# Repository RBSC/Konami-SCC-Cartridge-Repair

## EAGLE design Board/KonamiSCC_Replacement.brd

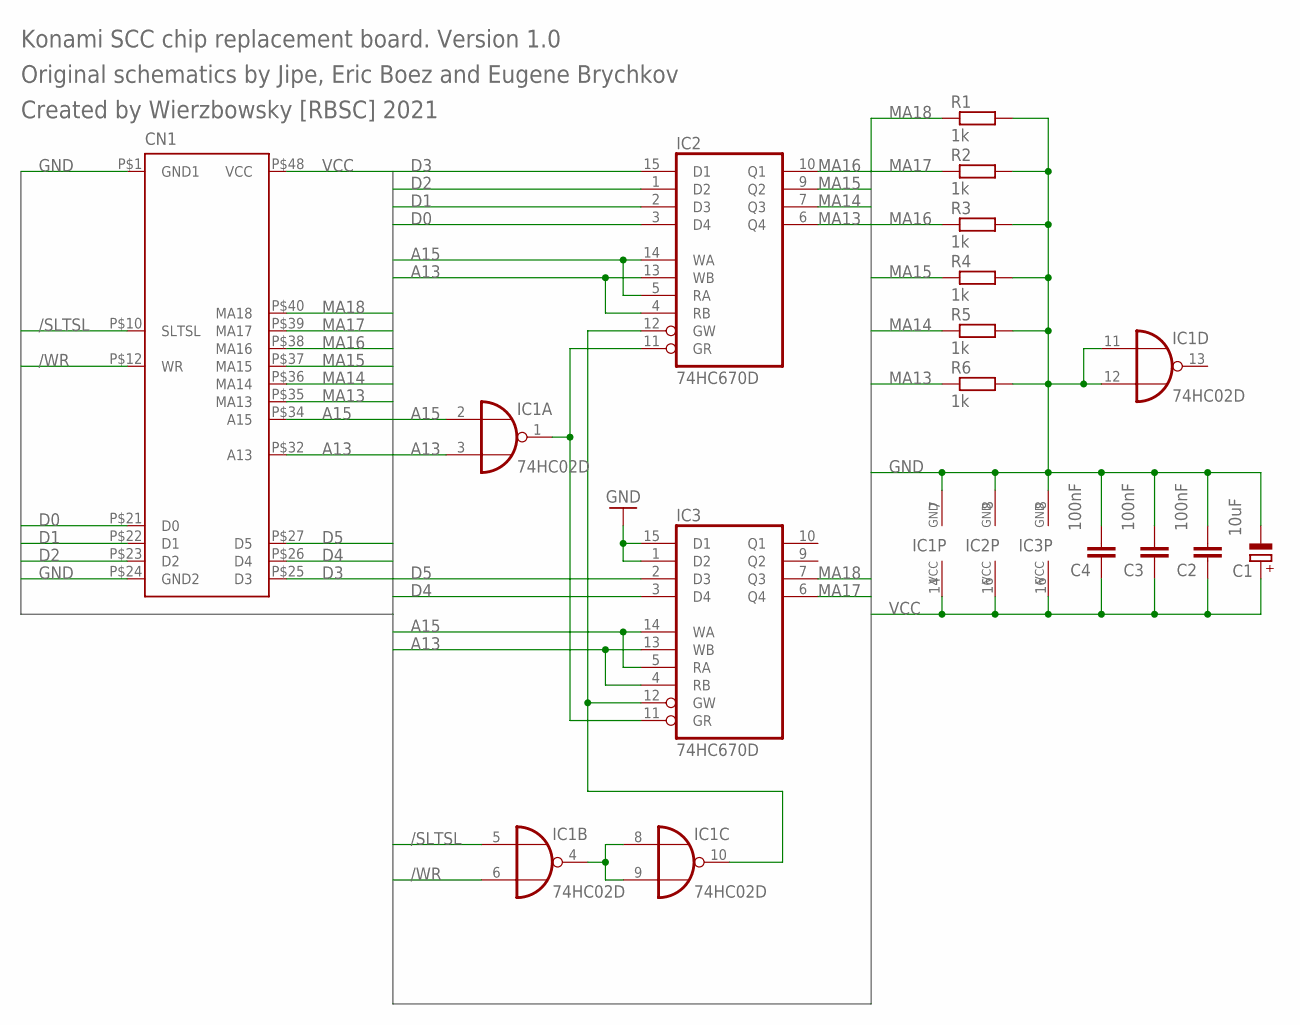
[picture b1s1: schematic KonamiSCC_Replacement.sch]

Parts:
C1: 10uF; SMC_C
C2, C3, C4: 100nF; C0805
CN1: 2212P003_PLACEHOLDERP; DIP48
IC1: 74HC02D; SO14
IC2, IC3: 74HC670D; SO16
R1, R2, R3, R4, R5, R6: 1k; M0805

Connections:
/SLTSL: CN1.P$10 (SLTSL), IC1.5 (I0)
/WR: CN1.P$12 (WR), IC1.6 (I1)
A13: CN1.P$32 (A13), IC1.3 (I1), IC2.4 (RB), IC2.13 (WB), IC3.4 (RB), IC3.13 (WB)
A15: CN1.P$34 (A15), IC1.2 (I0), IC2.5 (RA), IC2.14 (WA), IC3.5 (RA), IC3.14 (WA)
D0: CN1.P$21 (D0), IC2.3 (D4)
D1: CN1.P$22 (D1), IC2.2 (D3)
D2: CN1.P$23 (D2), IC2.1 (D2)
D3: CN1.P$25 (D3), IC2.15 (D1)
D4: CN1.P$26 (D4), IC3.3 (D4)
D5: CN1.P$27 (D5), IC3.2 (D3)
GND: C1.-, C2.2, C3.2, C4.2, CN1.P$1 (GND1), CN1.P$24 (GND2), IC1.7 (GND), IC1.11 (I0), IC1.12 (I1), IC2.8 (GND), IC3.1 (D2), IC3.8 (GND), IC3.15 (D1), R1.2, R2.2, R3.2, R4.2, R5.2, R6.2
MA13: CN1.P$35 (MA13), IC2.6 (Q4), R6.1
MA14: CN1.P$36 (MA14), IC2.7 (Q3), R5.1
MA15: CN1.P$37 (MA15), IC2.9 (Q2), R4.1
MA16: CN1.P$38 (MA16), IC2.10 (Q1), R3.1
MA17: CN1.P$39 (MA17), IC3.6 (Q4), R2.1
MA18: CN1.P$40 (MA18), IC3.7 (Q3), R1.1
unnamed: IC1.4 (O), IC1.8 (I0), IC1.9 (I1)
unnamed: IC1.10 (O), IC2.12 (GW), IC3.12 (GW)
unnamed: IC1.1 (O), IC2.11 (GR), IC3.11 (GR)
VCC: C1.+, C2.1, C3.1, C4.1, CN1.P$48 (VCC), IC1.14 (VCC), IC2.16 (VCC), IC3.16 (VCC)

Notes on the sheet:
Konami SCC chip replacement board. Version 1.0
Created by Wierzbowsky [RBSC] 2021
Original schematics by Jipe, Eric Boez and Eugene Brychkov

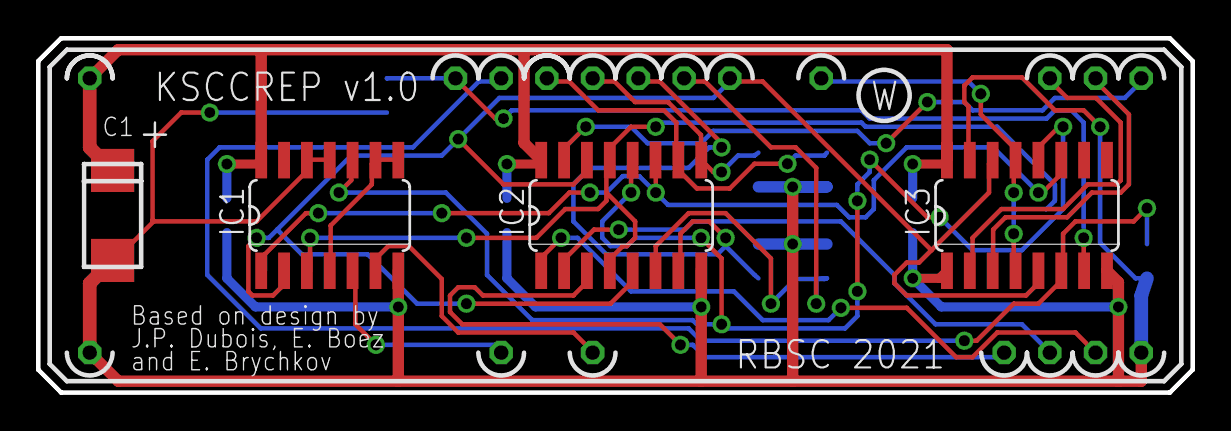
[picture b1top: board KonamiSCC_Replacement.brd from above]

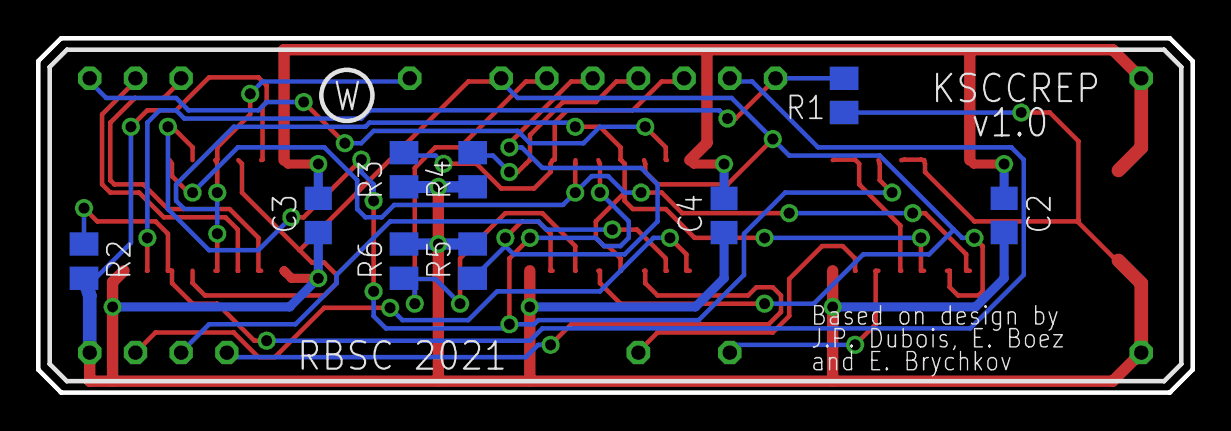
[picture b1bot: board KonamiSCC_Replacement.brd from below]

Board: 2 copper layers, 64.1 x 19.7 mm, 14 parts (9 on the bottom side), 21 nets.

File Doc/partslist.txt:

Partlist

Exported from KonamiSCC_Replacement.sch at 30-Jun-21 22:05

Assembly variant: 

Part     Value                 Device                Package  Library              Sheet

C1       10uF                  CPOL-EUSMCC           SMC_C    rcl                  1
C2       100nF                 C-EUC0805             C0805    rcl                  1
C3       100nF                 C-EUC0805             C0805    rcl                  1
C4       100nF                 C-EUC0805             C0805    rcl                  1
CN1      SCC_PLACEHOLDER       SCC_PLACEHOLDER       DIP48    SCC chip placeholder 1
IC1      74HC02D               74HC02D               SO14     74xx-eu              1
IC2      74HC670D              74HC670D              SO16     74xx-eu              1
IC3      74HC670D              74HC670D              SO16     74xx-eu              1
R1       1k                    R-EU_M0805            M0805    rcl                  1
R2       1k                    R-EU_M0805            M0805    rcl                  1
R3       1k                    R-EU_M0805            M0805    rcl                  1
R4       1k                    R-EU_M0805            M0805    rcl                  1
R5       1k                    R-EU_M0805            M0805    rcl                  1
R6       1k                    R-EU_M0805            M0805    rcl                  1

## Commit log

2021-07-01 :lollipop: Added .gitattributes & .gitignore files
2021-07-01 Initial release 01.07.2021
    Initial release
